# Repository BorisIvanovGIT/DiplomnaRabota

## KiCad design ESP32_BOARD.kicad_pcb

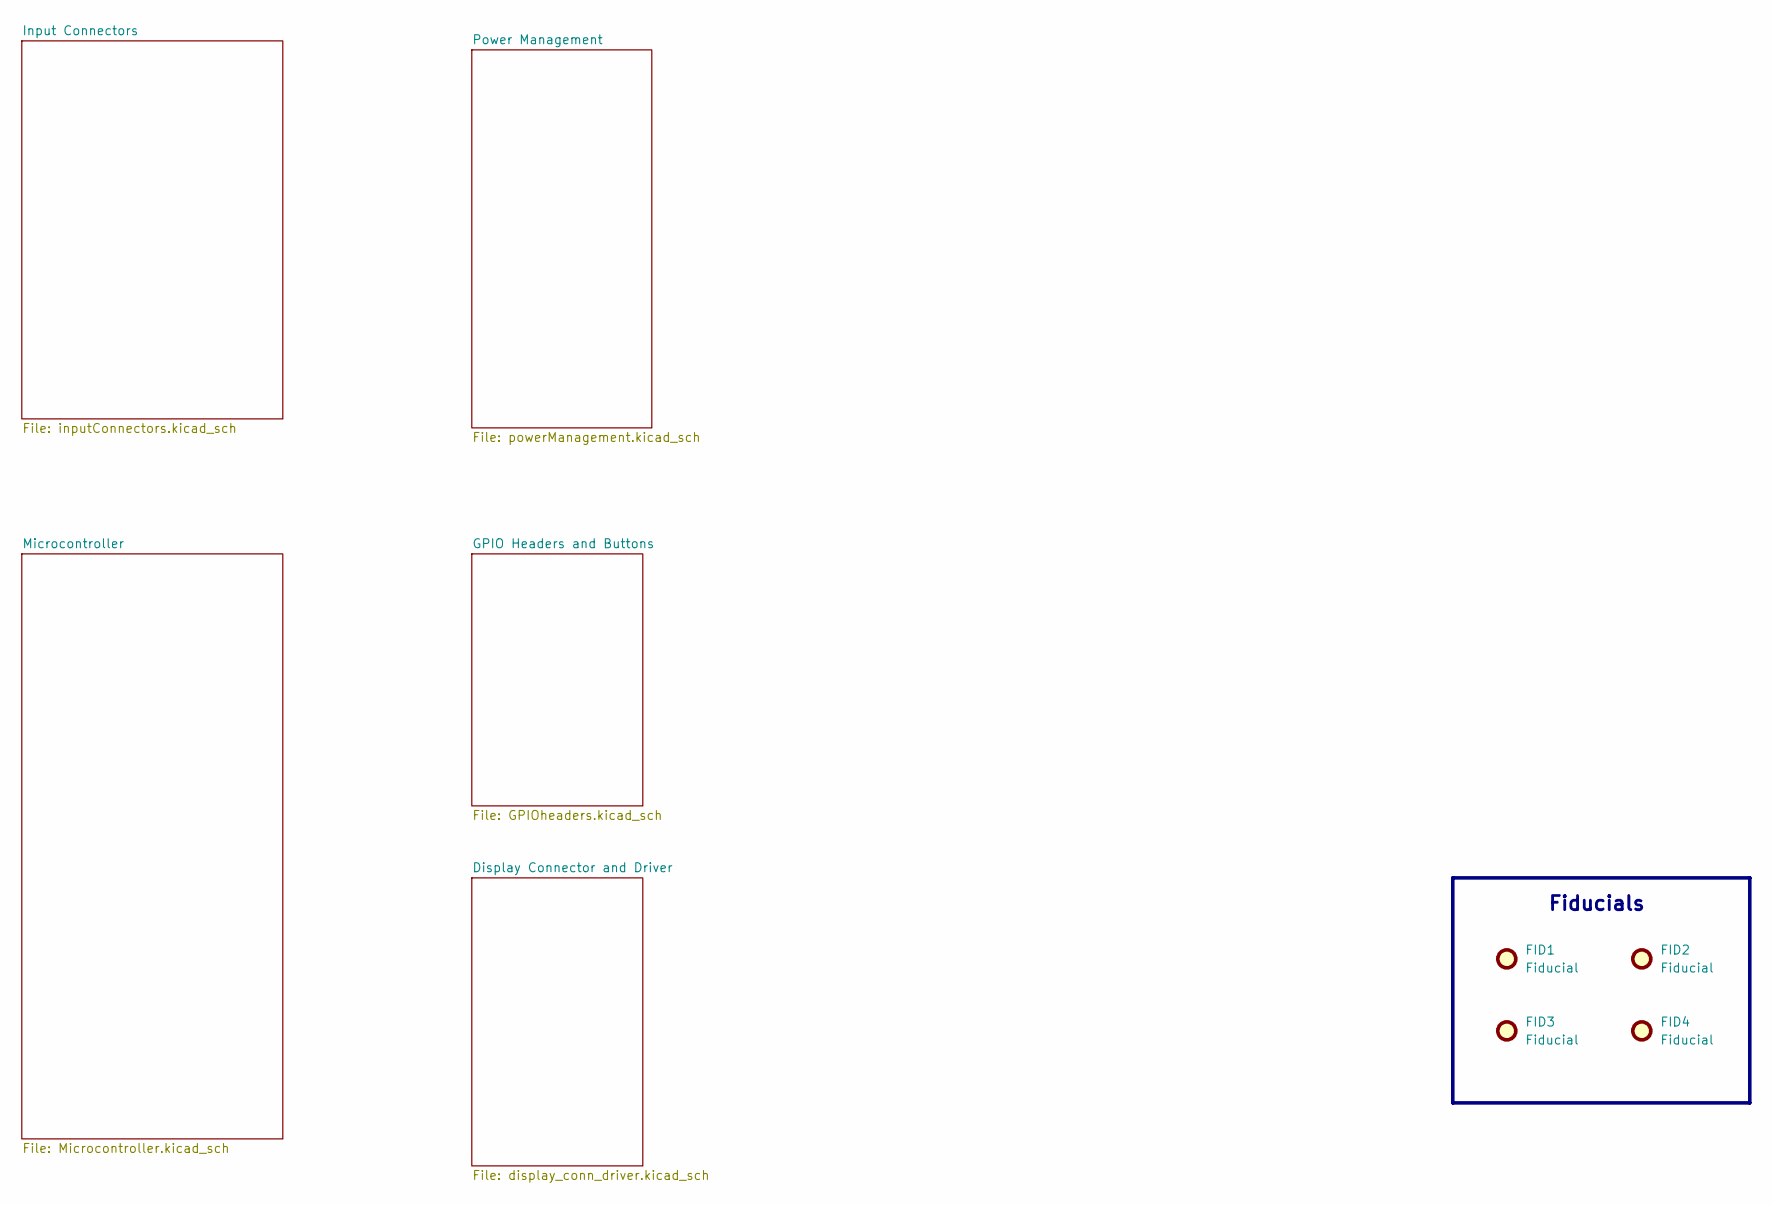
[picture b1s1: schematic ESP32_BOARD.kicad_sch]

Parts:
FID1, FID2, FID3, FID4: Fiducial; Fiducial_1mm_Mask2mm

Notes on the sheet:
Fiducials

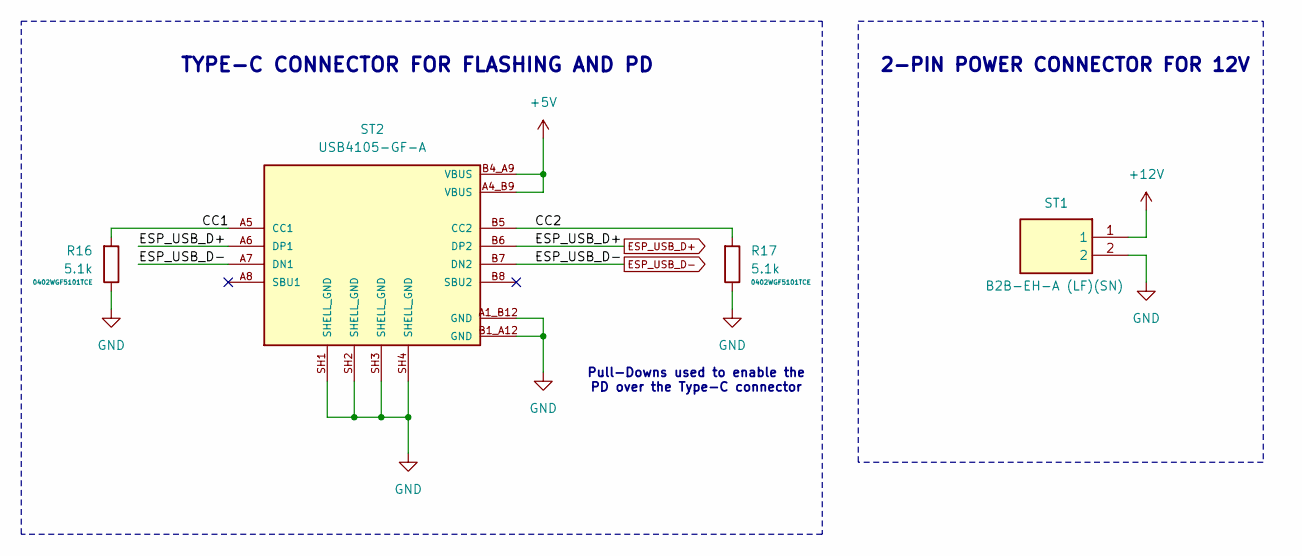
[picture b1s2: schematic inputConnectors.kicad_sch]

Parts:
R16, R17: 5.1k; RESC1005X40N
ST1: B2B-EH-A (LF)(SN); SHDR2W64P0X250_1X2_750X380X600P; Manufacturer_Part_Number B2B-EH-A(LF)(SN); Mouser Part Number N/A
ST2: USB4105-GF-A; GCT_USB4105-GF-A; PARTREV B4; DigiKey_Part_Number 2073-USB4105-GF-ATR-ND

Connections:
+5V: ST2.A4_B9 (VBUS), ST2.B4_A9 (VBUS); also elsewhere on the board
+12V: ST1.1; also elsewhere on the board
/Input Connectors/CC1: R16.1, ST2.A5 (CC1)
/Input Connectors/CC2: R17.1, ST2.B5 (CC2)
ESP_USB_D+: ST2.A6 (DP1), ST2.B6 (DP2); also elsewhere on the board
ESP_USB_D-: ST2.A7 (DN1), ST2.B7 (DN2); also elsewhere on the board
GND: R16.2, R17.2, ST1.2, ST2.A1_B12 (GND), ST2.B1_A12 (GND), ST2.SH1 (SHELL_GND), ST2.SH2 (SHELL_GND), ST2.SH3 (SHELL_GND), ST2.SH4 (SHELL_GND); also elsewhere on the board

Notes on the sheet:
2-PIN POWER CONNECTOR FOR 12V
Pull-Downs used to enable the PD over the Type-C connector
TYPE-C CONNECTOR FOR FLASHING AND PD

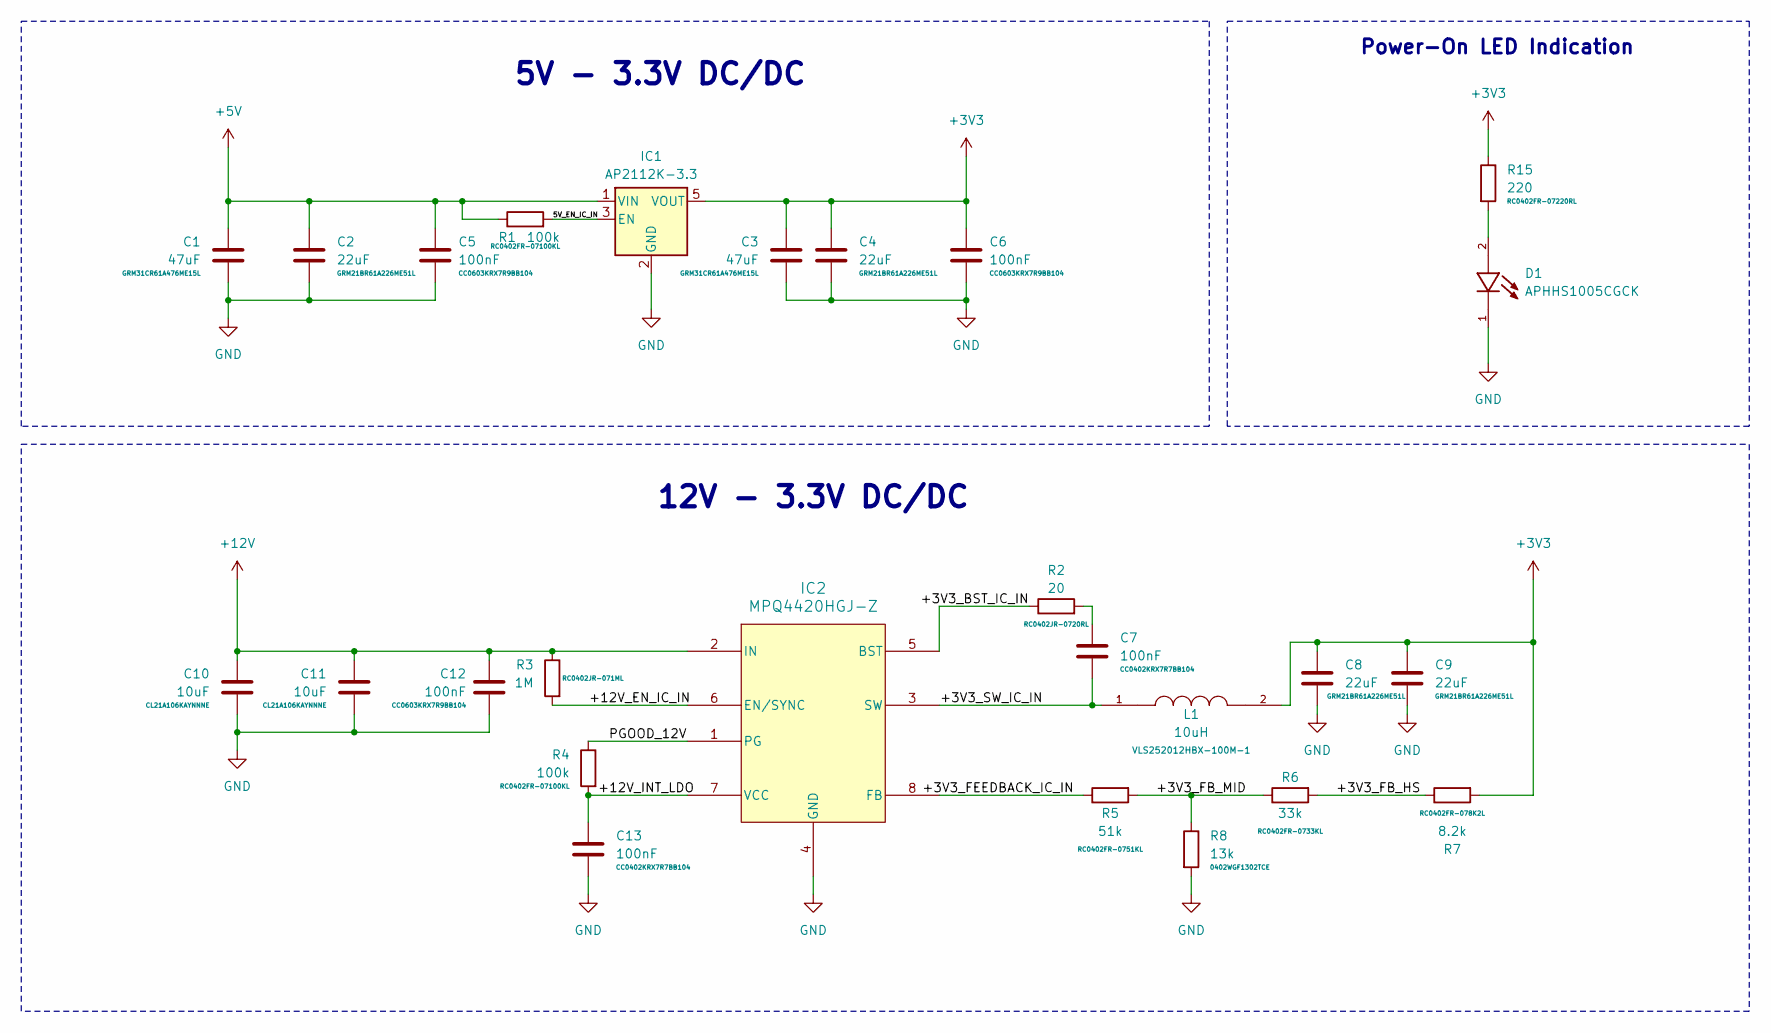
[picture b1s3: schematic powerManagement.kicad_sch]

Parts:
C1, C3: 47uF; CAPC3216X180N
C2, C4, C8, C9: 22uF; CAPC2012X140N
C5, C6, C12: 100nF; CC0603KRX7R9BB104
C7, C13: 100nF; CAPC1005X55N
C10, C11: 10uF; CAPC2012X135N
D1: APHHS1005CGCK; LED_APHHS1005CGCK; PARTREV V.9B
IC1: AP2112K-3.3; SOT-23-5
IC2: MPQ4420HGJ-Z; TSOT23-8_MPQ4420H_MNP
L1: 10uH; IND_VLS252012HBX-100M-1; PARTREV N/A
R1, R4: 100k; RC0402FR-07100KL
R2: 20; RESC1005X40N
R3: 1M; R0402
R5: 51k; RESC1005X40N
R6: 33k; RESC1005X40N
R7: 8.2k; RESC1005X40N
R8: 13k; RESC1005X40N
R15: 220; RESC1005X40N

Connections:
+3V3: C3.1, C4.1, C6.1, C8.1, C9.1, IC1.5 (VOUT), L1.2, R7.2, R15.1; also elsewhere on the board
+5V: C1.1, C2.1, C5.1, IC1.1 (VIN), R1.1; also elsewhere on the board
+12V: C10.1, C11.1, C12.1, IC2.2 (IN), R3.1; also elsewhere on the board
/Power Management/5V_EN_IC_IN: IC1.3 (EN), R1.2
/Power Management/+3V3_BST_IC_IN: IC2.5 (BST), R2.1
/Power Management/+3V3_FB_HS: R6.2, R7.1
/Power Management/+3V3_FB_MID: R5.2, R6.1, R8.1
/Power Management/+3V3_FEEDBACK_IC_IN: IC2.8 (FB), R5.1
/Power Management/+3V3_SW_IC_IN: C7.2, IC2.3 (SW), L1.1
/Power Management/+12V_EN_IC_IN: IC2.6 (EN/SYNC), R3.2
/Power Management/+12V_INT_LDO: C13.1, IC2.7 (VCC), R4.2
/Power Management/PGOOD_12V: IC2.1 (PG), R4.1
GND: C1.2, C2.2, C3.2, C4.2, C5.2, C6.2, C8.2, C9.2, C10.2, C11.2, C12.2, C13.2, D1.1, IC1.2 (GND), IC2.4 (GND), R8.2; also elsewhere on the board
unnamed: C7.1, R2.2
unnamed: D1.2, R15.2

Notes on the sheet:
5V - 3.3V DC/DC
12V - 3.3V DC/DC
Power-On LED Indication

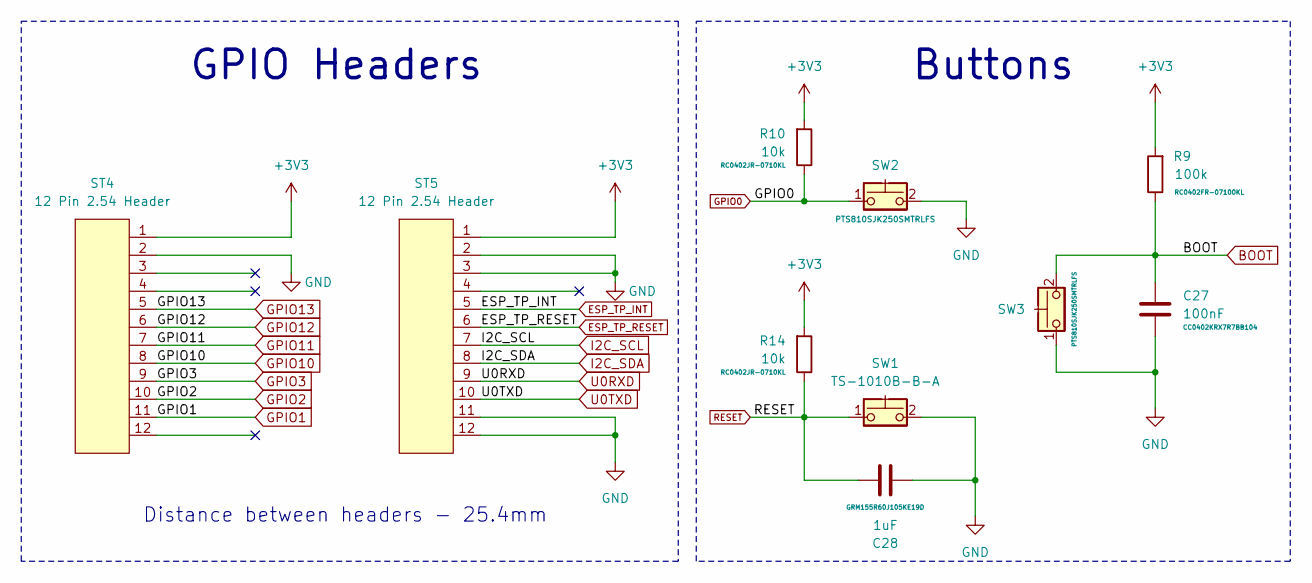
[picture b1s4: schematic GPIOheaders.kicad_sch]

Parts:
C27: 100nF; CAPC1005X55N
C28: 1uF; CAPC1005X55N
R9: 100k; RC0402FR-07100KL
R10, R14: 10k; RC0402JR-0710KL
ST4, ST5: 12 Pin 2.54 Header; X6511WV-12H-C60D30
SW1: TS-1010B-B-A; SW_010B-B-A_XKB
SW2, SW3: PTS810SJK250SMTRLFS; PTS810SJG250SMTRLFS

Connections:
+3V3: R9.2, R10.2, R14.2, ST4.1, ST5.1; also elsewhere on the board
BOOT: C27.1, R9.1, SW3.2; also elsewhere on the board
ESP_TP_INT: ST5.5; also elsewhere on the board
ESP_TP_RESET: ST5.6; also elsewhere on the board
GND: C27.2, C28.2, ST4.2, ST5.2, ST5.3, ST5.11, ST5.12, SW1.2, SW2.2, SW3.1; also elsewhere on the board
GPIO0: R10.1, SW2.1; also elsewhere on the board
GPIO1: ST4.11; also elsewhere on the board
GPIO2: ST4.10; also elsewhere on the board
GPIO3: ST4.9; also elsewhere on the board
GPIO10: ST4.8; also elsewhere on the board
GPIO11: ST4.7; also elsewhere on the board
GPIO12: ST4.6; also elsewhere on the board
GPIO13: ST4.5; also elsewhere on the board
I2C_SCL: ST5.7; also elsewhere on the board
I2C_SDA: ST5.8; also elsewhere on the board
RESET: C28.1, R14.1, SW1.1; also elsewhere on the board
U0RXD: ST5.9; also elsewhere on the board
U0TXD: ST5.10; also elsewhere on the board

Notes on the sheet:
Distance between headers - 25.4mm
Buttons
GPIO Headers

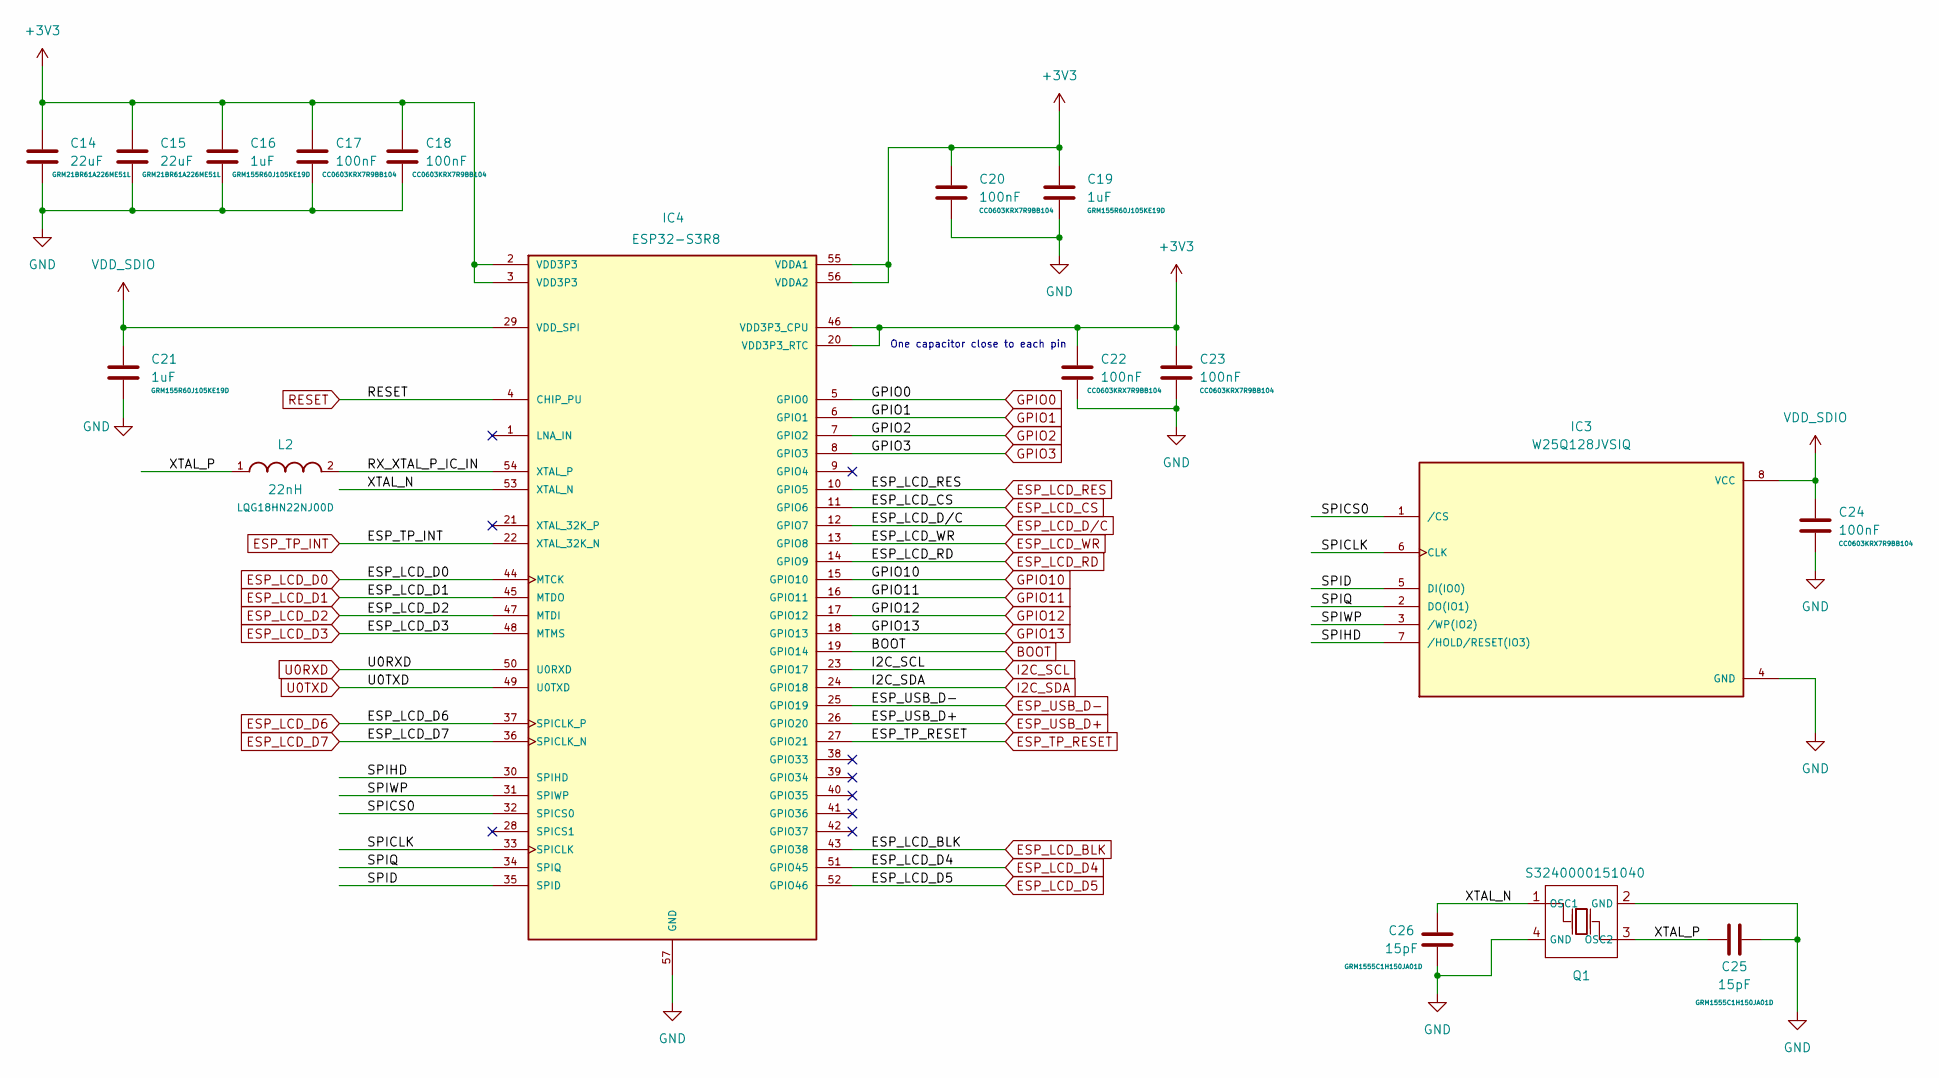
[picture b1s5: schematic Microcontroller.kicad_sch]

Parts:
C14, C15: 22uF; CAPC2012X140N
C16, C19, C21: 1uF; CAPC1005X55N
C17, C18, C20, C22, C23, C24: 100nF; CC0603KRX7R9BB104
C25, C26: 15pF; CAPC1005X55N
IC3: W25Q128JVSIQ; SOIC127P790X216-8N; PARTREV I
IC4: ESP32-S3R8; QFN40P700X700X90-57N
L2: 22nH; INDC1608X95N
Q1: 40MHz; CRYSTAL-SMD_4P-L3.2-W2.5-BL; Manufacturer Part S3240000151040; LCSC Part Name 40MHz ±10ppm 15pF

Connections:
+3V3: C14.1, C15.1, C16.1, C17.1, C18.1, C19.1, C20.1, C22.1, C23.1, IC4.2 (VDD3P3), IC4.3 (VDD3P3), IC4.20 (VDD3P3_RTC), IC4.46 (VDD3P3_CPU), IC4.55 (VDDA1), IC4.56 (VDDA2); also elsewhere on the board
/Microcontroller/RX_XTAL_P_IC_IN: IC4.54 (XTAL_P), L2.2
/Microcontroller/SPICLK: IC3.6 (CLK), IC4.33 (SPICLK)
/Microcontroller/SPICS0: IC3.1 (/CS), IC4.32 (SPICS0)
/Microcontroller/SPID: IC3.5 (DI(IO0)), IC4.35 (SPID)
/Microcontroller/SPIHD: IC3.7 (/HOLD/RESET(IO3)), IC4.30 (SPIHD)
/Microcontroller/SPIQ: IC3.2 (DO(IO1)), IC4.34 (SPIQ)
/Microcontroller/SPIWP: IC3.3 (/WP(IO2)), IC4.31 (SPIWP)
/Microcontroller/XTAL_N: C26.1, IC4.53 (XTAL_N), Q1.1 (OSC1)
/Microcontroller/XTAL_P: C25.1, L2.1, Q1.3 (OSC2)
BOOT: IC4.19 (GPIO14); also elsewhere on the board
ESP_LCD_BLK: IC4.43 (GPIO38); also elsewhere on the board
ESP_LCD_CS: IC4.11 (GPIO6); also elsewhere on the board
ESP_LCD_D0: IC4.44 (MTCK); also elsewhere on the board
ESP_LCD_D1: IC4.45 (MTDO); also elsewhere on the board
ESP_LCD_D2: IC4.47 (MTDI); also elsewhere on the board
ESP_LCD_D3: IC4.48 (MTMS); also elsewhere on the board
ESP_LCD_D4: IC4.51 (GPIO45); also elsewhere on the board
ESP_LCD_D5: IC4.52 (GPIO46); also elsewhere on the board
ESP_LCD_D6: IC4.37 (SPICLK_P); also elsewhere on the board
ESP_LCD_D7: IC4.36 (SPICLK_N); also elsewhere on the board
ESP_LCD_D/C: IC4.12 (GPIO7); also elsewhere on the board
ESP_LCD_RD: IC4.14 (GPIO9); also elsewhere on the board
ESP_LCD_RES: IC4.10 (GPIO5); also elsewhere on the board
ESP_LCD_WR: IC4.13 (GPIO8); also elsewhere on the board
ESP_TP_INT: IC4.22 (XTAL_32K_N); also elsewhere on the board
ESP_TP_RESET: IC4.27 (GPIO21); also elsewhere on the board
ESP_USB_D+: IC4.26 (GPIO20); also elsewhere on the board
ESP_USB_D-: IC4.25 (GPIO19); also elsewhere on the board
GND: C14.2, C15.2, C16.2, C17.2, C18.2, C19.2, C20.2, C21.2, C22.2, C23.2, C24.2, C25.2, C26.2, IC3.4 (GND), IC4.57 (GND), Q1.2 (GND), Q1.4 (GND); also elsewhere on the board
GPIO0: IC4.5 (GPIO0); also elsewhere on the board
GPIO1: IC4.6 (GPIO1); also elsewhere on the board
GPIO2: IC4.7 (GPIO2); also elsewhere on the board
GPIO3: IC4.8 (GPIO3); also elsewhere on the board
GPIO10: IC4.15 (GPIO10); also elsewhere on the board
GPIO11: IC4.16 (GPIO11); also elsewhere on the board
GPIO12: IC4.17 (GPIO12); also elsewhere on the board
GPIO13: IC4.18 (GPIO13); also elsewhere on the board
I2C_SCL: IC4.23 (GPIO17); also elsewhere on the board
I2C_SDA: IC4.24 (GPIO18); also elsewhere on the board
RESET: IC4.4 (CHIP_PU); also elsewhere on the board
U0RXD: IC4.50 (U0RXD); also elsewhere on the board
U0TXD: IC4.49 (U0TXD); also elsewhere on the board
VDD_SDIO: C21.1, C24.1, IC3.8 (VCC), IC4.29 (VDD_SPI)

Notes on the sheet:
One capacitor close to each pin

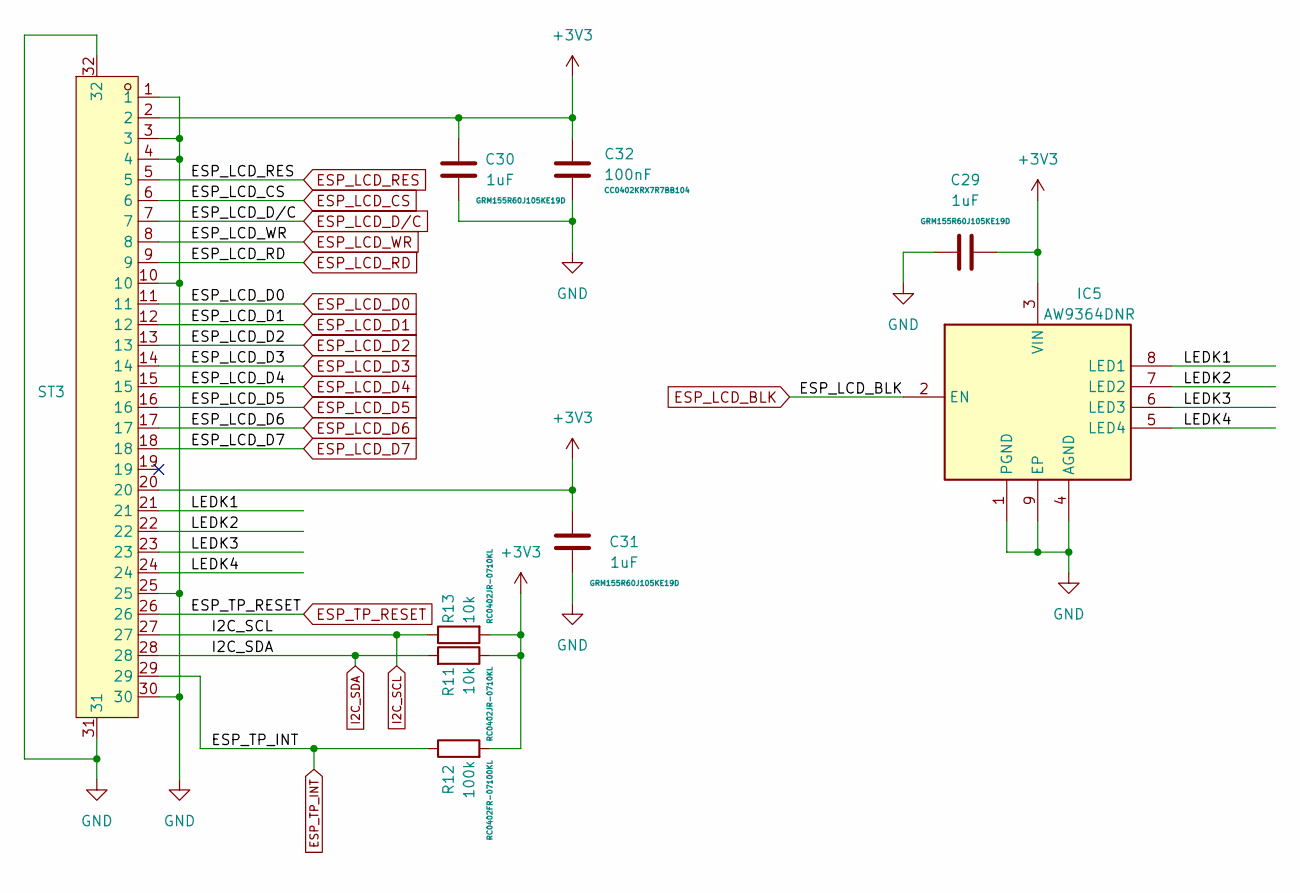
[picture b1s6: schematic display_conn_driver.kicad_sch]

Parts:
C29, C30, C31: 1uF; CAPC1005X55N
C32: 100nF; CAPC1005X55N
IC5: AW9364DNR; SON50P200X200X80-9N-D; Manufacturer_Part_Number AW9364DNR
R11, R13: 10k; RC0402JR-0710KL
R12: 100k; RC0402FR-07100KL
ST3: KH-CL0.5-H2.0-30PIN; Manufacturer Part KH-CL0.5-H2.0-30PIN

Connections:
+3V3: C29.1, C30.1, C31.1, C32.1, IC5.3 (VIN), R11.1, R12.2, R13.2, ST3.2, ST3.20; also elsewhere on the board
/Display Connector and Driver/LEDK1: IC5.8 (LED1), ST3.21
/Display Connector and Driver/LEDK2: IC5.7 (LED2), ST3.22
/Display Connector and Driver/LEDK3: IC5.6 (LED3), ST3.23
/Display Connector and Driver/LEDK4: IC5.5 (LED4), ST3.24
ESP_LCD_BLK: IC5.2 (EN); also elsewhere on the board
ESP_LCD_CS: ST3.6; also elsewhere on the board
ESP_LCD_D0: ST3.11; also elsewhere on the board
ESP_LCD_D1: ST3.12; also elsewhere on the board
ESP_LCD_D2: ST3.13; also elsewhere on the board
ESP_LCD_D3: ST3.14; also elsewhere on the board
ESP_LCD_D4: ST3.15; also elsewhere on the board
ESP_LCD_D5: ST3.16; also elsewhere on the board
ESP_LCD_D6: ST3.17; also elsewhere on the board
ESP_LCD_D7: ST3.18; also elsewhere on the board
ESP_LCD_D/C: ST3.7; also elsewhere on the board
ESP_LCD_RD: ST3.9; also elsewhere on the board
ESP_LCD_RES: ST3.5; also elsewhere on the board
ESP_LCD_WR: ST3.8; also elsewhere on the board
ESP_TP_INT: R12.1, ST3.29; also elsewhere on the board
ESP_TP_RESET: ST3.26; also elsewhere on the board
GND: C29.2, C30.2, C31.2, C32.2, IC5.1 (PGND), IC5.4 (AGND), IC5.9 (EP), ST3.1, ST3.3, ST3.4, ST3.10, ST3.25, ST3.30, ST3.31, ST3.32; also elsewhere on the board
I2C_SCL: R13.1, ST3.27; also elsewhere on the board
I2C_SDA: R11.2, ST3.28; also elsewhere on the board

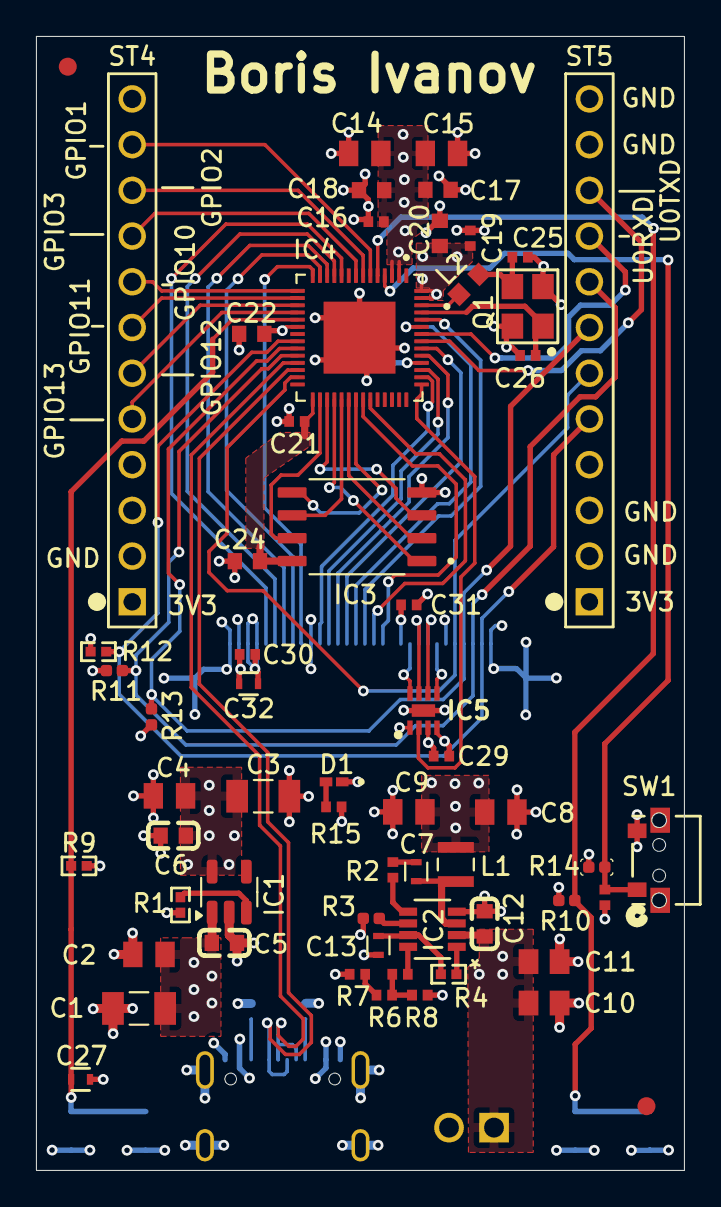
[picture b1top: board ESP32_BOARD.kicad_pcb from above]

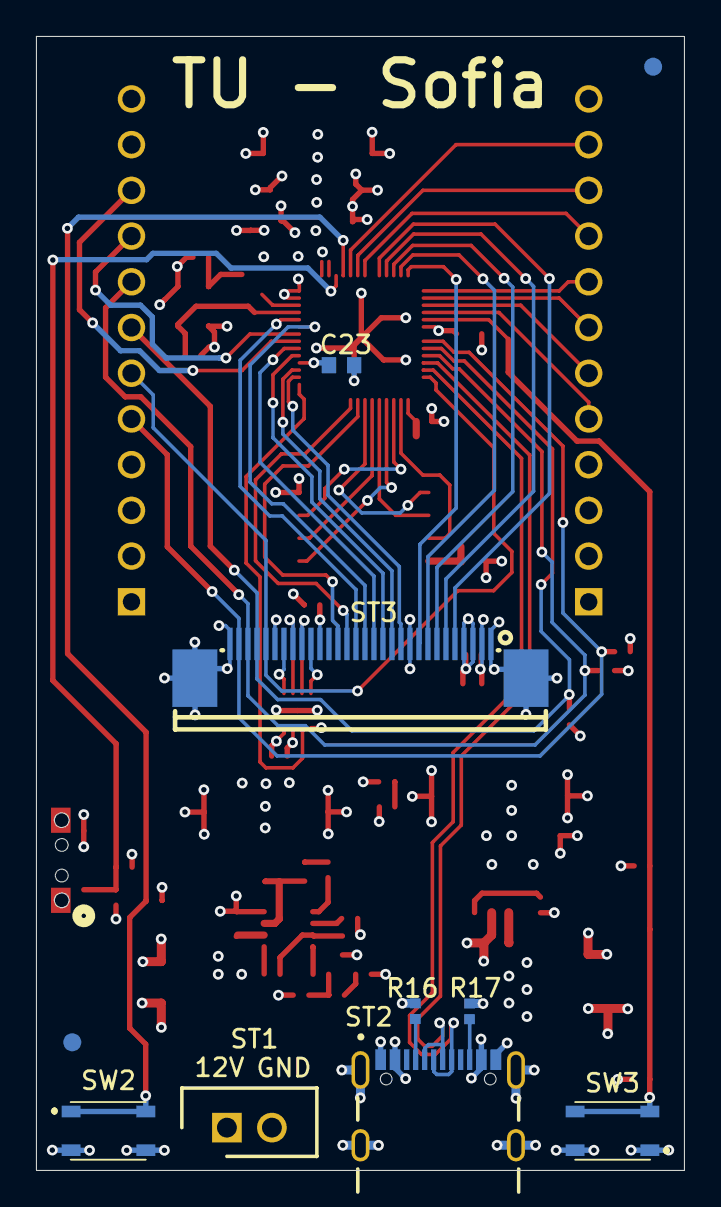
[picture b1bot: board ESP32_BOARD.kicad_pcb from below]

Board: 4 copper layers, 36.0 x 63.0 mm, 70 parts (10 on the bottom side), 63 nets.

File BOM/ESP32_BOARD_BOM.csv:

Designator;Quanity;Comment;Footprint;Datasheet
C1,C3;2;47uF;GRM31CR61A476ME15L:CAPC3216X180N;~
C2,C4,C8,C9,C14,C15;6;22uF;GRM21BR61A226ME51L:CAPC2012X140N;~
C5,C6,C12,C17,C18,C20,C22,C23,C24;9;100nF;CC0603KRX7R9BB104:CC0603KRX7R9BB104;~
C7,C13,C27,C32;4;100nF;CC0402KRX7R7BB104:CAPC1005X55N;~
C10,C11;2;10uF;CL21A106KAYNNNE:CAPC2012X135N;~
C16,C19,C21,C28,C29,C30,C31;7;1uF;GRM155R60J105KE19D:CAPC1005X55N;~
C25,C26;2;15pF;GRM1555C1H150JA01D:CAPC1005X55N;~
D1;1;APHHS1005CGCK;APHHS1005CGCK:LED_APHHS1005CGCK;
IC1;1;AP2112K-3.3;Package_TO_SOT_SMD:SOT-23-5;https://www.diodes.com/assets/Datasheets/AP2112.pdf
IC2;1;MPQ4420HGJ-Z;MPQ4420HGJ-Z:TSOT23-8_MPQ4420H_MNP;MPQ4420HGJ-Z
IC3;1;W25Q128JVSIQ;W25Q128JVSIQ:SOIC127P790X216-8N;
IC4;1;ESP32-S3R8;ESP32-S3R8:QFN40P700X700X90-57N;
IC5;1;AW9364DNR;AW9364DNR:SON50P200X200X80-9N-D;https://datasheet.lcsc.com/szlcsc/1912111437_AWINIC-Shanghai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
L1;1;10uH;VLS252012HBX-100M-1:IND_VLS252012HBX-100M-1;
L2;1;22nH;LQG18HN22NJ00D:INDC1608X95N;
Q1;1;40MHz;S3240000151040:CRYSTAL-SMD_4P-L3.2-W2.5-BL;https://atta.szlcsc.com/upload/public/pdf/source/20191012/C4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
R1,R4,R9,R12;4;100k;RC0402FR-07100KL:RC0402FR-07100KL;~
R2;1;20;RC0402JR-0720RL:RESC1005X40N;~
R3;1;1M;RC0402JR-071ML:R0402;~
R5;1;51k;RC0402FR-0751KL:RESC1005X40N;~
R6;1;33k;RC0402FR-0733KL:RESC1005X40N;~
R7;1;8.2k;RC0402FR-078K2L:RESC1005X40N;~
R8;1;13k;0402WGF1302TCE:RESC1005X40N;~
R10,R11,R13,R14;4;10k;RC0402JR-0710KL:RC0402JR-0710KL;~
R15;1;220;RC0402FR-07220RL:RESC1005X40N;~
R16,R17;2;5.1k;0402WGF5101TCE:RESC1005X40N;~
ST1;1;B2B-EH-A (LF)(SN);JST_B2B-EH-A(LF)(SN):SHDR2W64P0X250_1X2_750X380X600P;http://www.farnell.com/datasheets/2057210.pdf
ST2;1;USB4105-GF-A;TYPE-C-USB4105-GF-A:GCT_USB4105-GF-A;
ST3;1;~;KH-CL0.5-H2.0-30PIN:KH-CL0.5-H2.0-30PIN;
ST4,ST5;2;12 Pin 2.54 Header;12P_2.54_X6511WV-12H-C60D30:X6511WV-12H-C60D30;~
SW1;1;TS-1010B-B-A;TS-1010B-B-A:SW_010B-B-A_XKB;https://www.ckswitches.com/media/1482/kms.pdf
SW2,SW3;2;PTS810SJK250SMTRLFS;PTS810SJK250SMTRLFS:PTS810SJG250SMTRLFS;https://www.ckswitches.com/media/1482/kms.pdf

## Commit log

2025-04-12 Commit test
2025-04-12 Test 2
2025-04-12 test 3
2025-04-12 test 4
2025-04-13 Crystal Change
    Crystal changed from active (CMSO) to passive with 2x 15pF load capacitors
2025-04-13 Some small fixes
    Swapped the pins on the oscillator
2025-04-13 Last commit
2025-04-14 Changes to final schematic
2025-04-15 Layout Started
    Board setup done, DC/DC Converters arranged and slight changes tot he board outline.
2025-04-15 Arranged Headers + Added pull-down resistors for type-c conn
2025-04-16 JST 2 PIN CONN Changed + Additional 3D Models added
2025-04-17 Origin of PCB Layout changed
2025-04-21 Lazy Layout Done
    Needed additional movement of the components to achieve better routing
2025-04-22 Most of the layout done
2025-04-23 Routing done | First Iteration
    Silkscreen of components kinda done
2025-04-23 Minor adjustments to the layout and the silkscreen
2025-04-24 Layout ready for export
2025-04-24 Finished Layout | Ver. 1.0
    Layout finished for ver. 1.0
    Design at a stage before the review from the colleagues
2025-04-24 Gerbers and BOM Generated
    Gerbers and BOM are generated and added to the project folder
2025-04-24 Problems with manufacturing files
2025-04-24 BOM Files Fixed
2025-04-24 Gerb Files Fixed | Drill File Updated
2025-04-28 PCB Review Documents Generated
2025-05-29 Minor changes to styling
2025-06-24 Промяна по оформление и текст в схемата
2025-06-29 Backups
